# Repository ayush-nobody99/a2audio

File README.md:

# 🎧 a2audio — High-Fidelity Audio DAC/AMP Board

> playback, for the purist.

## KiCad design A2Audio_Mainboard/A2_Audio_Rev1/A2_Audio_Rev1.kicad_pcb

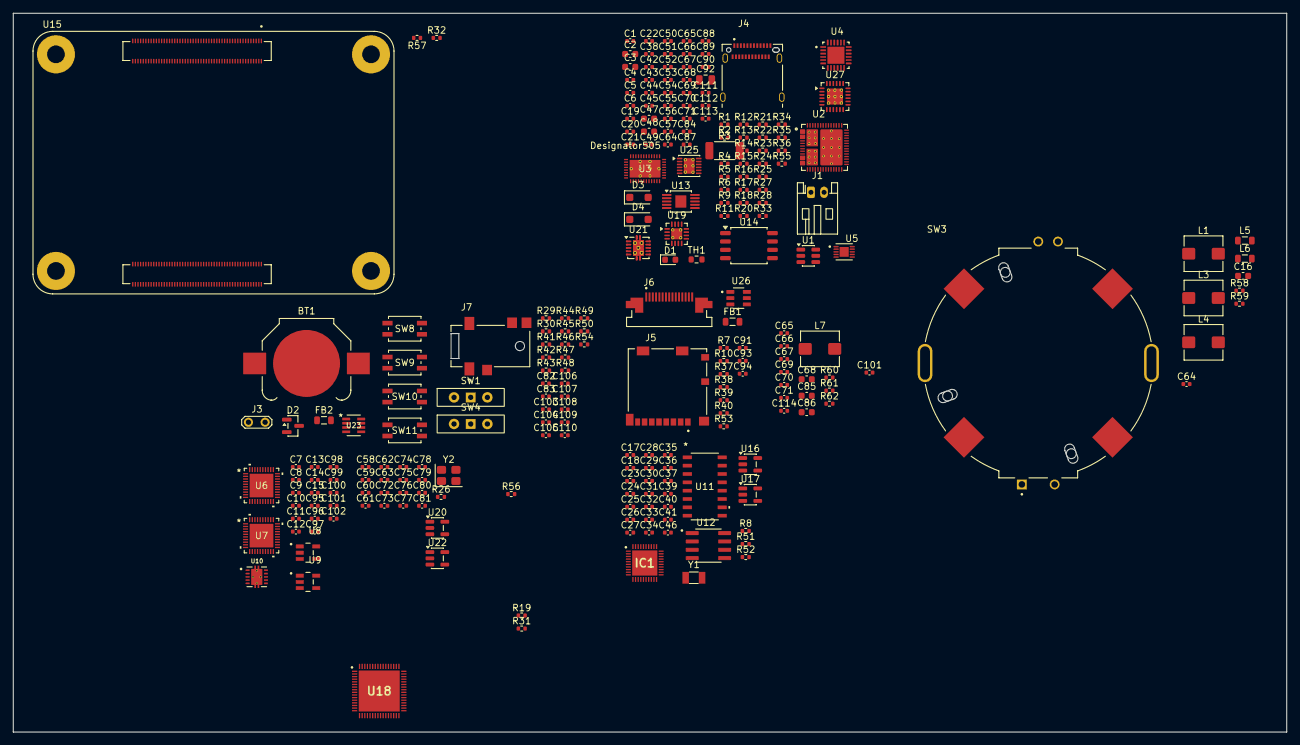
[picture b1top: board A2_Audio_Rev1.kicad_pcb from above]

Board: 4 copper layers, 194.0 x 109.5 mm, 241 parts (0 on the bottom side), 223 nets, no tracks yet.

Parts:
BT1: CR1220; BatteryHolder_Keystone_3000_1x12mm
C1, C7, C8, C9, C39, C40, C41, C46, C71, C96, C97, C99, C100, C103, C113: 1µF; C_0402_1005Metric
C2, C3, C47, C48, C85, C86: 22µF; C_0603_1608Metric
C4, C14, C15, C27, C32, C33, C64, C66#2, C91, C94: 10µF; C_0402_1005Metric
C5, C10, C13, C20, C21, C22, C84, C88, C89, C90, C111: 4.7µF; C_0402_1005Metric
C6: 47nF; C_0402_1005Metric
C11, C12, C24, C25, C34, C35, C36, C37, C53, C95, C98, C101, C102: 2.2µF; C_0402_1005Metric
C16: 10µF; C_0603_1608Metric
C17, C18, C23, C26, C28, C29, C30, C31, C38, C42, C43, C44, C45, C56, C65#2, C67, C83, C87, C112, C114: 0.1µF; C_0402_1005Metric
C19: 0.47µF; C_0402_1005Metric
C49: 3.3nF; C_0402_1005Metric
C50, C51, C52, C64#2, C65, C66, C67#2, C68, C69#2, C70, C71#2, C72, C73, C74, C75, C76, C77, C78, C79, C80, C81, C93, C101#2, C105, C106, C107, C108, C109, C110: 100nF; C_0402_1005Metric
C54: 10nF; C_0402_1005Metric
C55, C57: 22µF; C_0402_1005Metric
C58, C59, C60, C61: 1μF; C_0402_1005Metric
C62, C63: 22pF; C_0402_1005Metric
C68#2: 47nF; C_0603_1608Metric
C69: 4.7nF; C_0402_1005Metric
C70#2: 220pF; C_0402_1005Metric
C82: 0.33µF; C_0402_1005Metric
C92: 22µF; C_0805_2012Metric
C104: 100pF; C_0402_1005Metric
D1: LED; LED_0603_1608Metric
D2: BAT54C; SOT-23
D3, D4: PMEG2020EH; D_SOD-123F
FB1: 600 Ohms @ 100MHz; L_0805_2012Metric
FB2: FerriteBead; L_0805_2012Metric
IC1: ES9822QPRO; QFN40P500X500X80-41N-D
J1: Battery_Connector; JST_PH_S2B-PH-K_1x02_P2.00mm_Horizontal
J3: BOOT_JUMPER; TestPoint_2Pads_Pitch2.54mm_Drill0.8mm
J4: 12401610E4_2A; AMPHENOL_12401610E4_2A
J5: 104031-0811; MOLEX_104031-0811
J6: SFV15R-1STE1HLF; AMPHENOL_SFV15R-1STE1HLF
J7: SJ2-35954B-SMT-TR; CUI_SJ2-35954B-SMT-TR
L1: 1µH; L_Bourns_SRP5030T
L3: 2.2µH; L_Bourns_SRP5030T
L4, L7: 1.0µH; L_Bourns_SRP5030T
L5, L6: 4.7µH; L_0805_2012Metric
R1, R2: 4.7k; R_0402_1005Metric
R3: 10mΩ; R_2010_5025Metric
R4, R5: 45.3kΩ; R_0402_1005Metric
R6, R7, R8, R10, R13, R21, R22, R23, R25, R37, R38, R39, R41, R42, R43, R44, R45, R46, R47, R48, R50, R51, R52, R53, R54, R62: 10kΩ; R_0402_1005Metric
R9: 1kΩ; R_0402_1005Metric
R11: 4.42 kΩ; R_0402_1005Metric
R12: 23.7 kΩ; R_0402_1005Metric
R14, R16, R17, R18, R20, R27, R35, R40, R58, R59: 100kΩ; R_0402_1005Metric
R15: 32.4kΩ; R_0402_1005Metric
R19, R31: 4.7kΩ; R_0402_1005Metric
R24: 180Ω; R_0402_1005Metric
R26: 2kΩ; R_0402_1005Metric
R28: 402kΩ; R_0402_1005Metric
R29: 10k; R_0402_1005Metric
R30: 100k; R_0402_1005Metric
R32, R56, R57: 22Ω; R_0402_1005Metric
R33: 205kΩ; R_0402_1005Metric
R34: 1.0MΩ; R_0402_1005Metric
R36: 124kΩ; R_0402_1005Metric
R49: 2.2kΩ; R_0402_1005Metric
R55: 31.6kΩ; R_0402_1005Metric
R60: 120kΩ; R_0402_1005Metric
R61: 15kΩ; R_0402_1005Metric
SW1, SW4: SW_Wuerth_450301014042; SW_Slide-03_Wuerth-WS-SLTV_10x2.5x6.4_P2.54mm
SW3: RotaryEncoder_Switch; XDCR_RING35-203010-TH
SW8, SW9, SW10, SW11: EVQ-PUJ02K; SW_EVQPUJ_4P7X3P5_PAN
TH1: 10kΩ NTC; R_0603_1608Metric
U1: USBLC6-2SC6; SOT-23-6
U2: TPS65987DDHRSHR; IC_TPS65987DDHRSHR
U3: TUSB546A-DCIRNQR; RNQ0040A
U4: BQ25895RTWR; QFN50P400X400X80-25N
U5: MAX17055ETB_T; SON40P200X250X80-11N
U6: U_DAC_L; QFN_CS43198_CIR
U7: U_DAC_R; QFN_CS43198_CIR
U8: TPS7A2018PDBVR; SOT95P280X145-5N
U9: TPS7A2033PDBVR; SOT95P280X145-5N
U10: OPA1622IDRCR; IC_OPA1622IDRCR
U11: SI4732-A10-GS; SOIC_A10-GS_SIL
U12: OPA1612AIDR; SOIC127P599X175-8N
U13: LT3042xMSE; MSOP-10-1EP_3x3mm_P0.5mm_EP1.68x1.88mm
U14: W25Q16JVSS; SOIC-8_5.3x5.3mm_P1.27mm
U15: CM5108000; MODULE_CM5108000
U16: AP2112K-3.3; SOT-23-5
U17, U20: AP2112K-1.8; SOT-23-5
U18: LT6711A; QFN40P750X750X80-65N-D
U19: TPS62130; VQFN-16-1EP_3x3mm_P0.5mm_EP1.68x1.68mm_ThermalVias
U21: TPS61230DRC; Texas_S-PVSON-N10_ThermalVias
U22: AP2112K-1.2; SOT-23-5
U23: LTC2954ITS8-1_TRPBF; TSOT-23_TS8
U25: LT3094xDD; DFN-12-1EP_3x3mm_P0.45mm_EP1.65x2.38mm_ThermalVias
U26: TS5A3159DBVR; SOT95P280X145-6N
U27: TPS65131RGE; VQFN-24-1EP_4x4mm_P0.5mm_EP2.45x2.45mm_ThermalVias
Y1: Crystal; Crystal_SMD_3215-2Pin_3.2x1.5mm
Y2: 27MHz; Crystal_SMD_3225-4Pin_3.2x2.5mm

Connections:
+5V(INPUT): C55.1, C56.1, C57.1, C85.1, C86.1, C114.1, R28.1, U15.77 (+5V(INPUT)), U15.79 (+5V(INPUT)), U15.81 (+5V(INPUT)), U15.83 (+5V(INPUT)), U15.85 (+5V(INPUT)), U15.87 (+5V(INPUT)), U21.3 (VOUT), U21.4 (VOUT)
/+3V3_SYS: C48.1, C51.1, C58.1, C59.2, C91.1, C93.1, C101#2.1, J5.4 (VDD), J6.14, J6.15, L3.2, R14.2, R16.1, R58.2, U2.5 (VIN_3V3), U3.1 (VCC), U3.6 (VCC), U3.20 (VCC), U3.28 (VCC), U18.8 (VCC33R), U18.20 (VCC33IO), U18.21 (VDD), U18.30 (VCC33STBY), U18.55 (VDD), U18.57 (VCC33IO), U19.14 (VOS), U20.1 (VIN), U20.3 (EN), U22.1 (VIN), U22.3 (EN), U26.3 (NC), U26.5 (V+)
/Audio_Engine/1V8_DIG: C8.1, U6.4 (VD), U6.7 (VA), U6.25 (VCP), U6.28 (*RESET), U6.31 (VL), U7.4 (VD), U7.7 (VA), U7.25 (VCP), U7.28 (*RESET), U7.30 (ADR), U7.31 (VL), U8.5 (OUT)
/Audio_Engine/3V3_ANA: C9.1, R19.2, R31.2, U6.26 (VP), U7.26 (VP), U9.5 (OUT), U10.8 (EN)
/Audio_Engine/AUDIO_OUT_L: U6.14 (HPOUTA), U10.1 (+INA)
/Audio_Engine/AUDIO_OUT_R: U7.14 (HPOUTA), U10.5 (+INB)
/Audio_Engine/HP_OUT_L: J7.2, U10.9 (OUTA), U10.10 (-INA)
/Audio_Engine/HP_OUT_R: J7.3, U10.6 (-INB), U10.7 (OUTB)
/BAT_ALRT: R21.1, U5.8 (ALRT), U15.30 (GPIO6)
/BT: R43.1, SW1.1 (B), U15.91 (BT_~DISABLE)
/BTN_INT: R29.2, U15.29 (GPIO16), U23.5 (*INT)
/BTN_KILL: R30.2, U15.24 (GPIO26), U23.8 (*KILL)
/CARD_DETECT: J5.10 (SW-2), R53.1, U15.37 (GPIO7)
/CHG_INT: R22.1, U4.7 (INT), U15.34 (GPIO5)
/ENC_1: C105.1, R42.2, SW3.A, U15.38 (GPIO11)
/ENC_2: C106.1, R44.2, SW3.B, U15.39 (GPIO8)
/ENC_SW: C107.1, R45.2, U15.40 (GPIO9)
/FM_ANT: C104.2, U11.6 (FMI)
/HP_DETECT: J7.10, R54.1, U15.55 (GPIO14)
/HP_GOOD_OUT: R6.1, U13.4 (PG), U15.47 (GPIO23), U25.4 (PG)
/I2C_SCL: R2.2, U2.27 (I2C1_SCL), U4.5 (SCL), U5.3 (SCL), U11.11 (SCLK), U15.56 (GPIO3), U18.17 (CSCL)
/I2C_SCL_AUDIO: IC1.26 (SCLK/SCL), R19.1, U6.1 (SCL), U7.1 (SCL), U15.28 (GPIO13)
/I2C_SDA: R1.2, U2.28 (I2C1_SDA), U4.6 (SDA), U5.4 (SDA), U11.12 (SDIO), U15.58 (GPIO2), U18.16 (CSDA)
/I2C_SDA_AUDIO: IC1.25 (MOSI/SDA), R31.1, U6.39 (SDA), U7.39 (SDA), U15.31 (GPIO12)
/I2S_BCLK: IC1.38 (GPIO2), U6.34 (SCLK1), U7.34 (SCLK1), U15.49 (GPIO18)
/I2S_DATA_IN: U6.2 (SDIN1), U7.2 (SDIN1), U15.25 (GPIO21)
/I2S_DATA_OUT: IC1.39 (GPIO1), U15.27 (GPIO20)
/I2S_LRCLK: IC1.37 (GPIO3), U6.38 (LRCK1), U7.38 (LRCK1), U15.26 (GPIO19)
/I2S_MCLK: R32.2, R56.1, R57.2, U15.54 (GPIO4)
/MIC_IN: R50.2, R51.2, U12.3 (+IN_A)
/MIPI1_C_N: J6.5, U15.187 (MIPI1_C_N)
/MIPI1_C_P: J6.6, U15.189 (MIPI1_C_P)
/MIPI1_D0_N: J6.8, U15.175 (MIPI1_D0_N)
/MIPI1_D0_P: J6.9, U15.177 (MIPI1_D0_P)
/MIPI1_D1_N: J6.2, U15.181 (MIPI1_D1_N)
/MIPI1_D1_P: J6.3, U15.183 (MIPI1_D1_P)
/NEXT: C109.1, R47.2, SW10.1, U15.45 (GPIO24)
/PD_IRQ: R25.1, U2.29 (~I2C1_IRQ), U15.46 (GPIO22)
/PLAY: C110.1, R48.2, SW11.1, U15.44 (GPIO10)
/PMIC_EN: U15.99 (PMIC_ENABLE), U23.6 (EN/*EN)
/PREV: C108.1, R46.2, SW9.1, U15.41 (GPIO25)
/PWR_BUTTON: D2.1, U4.12 (~QON)
/Power&Battery/+6V_DIRTY: C20.2, C84.1, C87.1, D3.1 (K), R36.2, U13.1 (IN), U13.2 (IN), U13.3 (EN/UV), U13.6 (PGFB), U27.23 (VPOS)
/Power&Battery/-6V_DIRTY: C90.2, C111.1, C112.1, D4.2 (A), R34.2, U25.1 (IN), U25.2 (IN), U25.3 (EN/UV), U25.5 (PGFB), U25.7 (VIOC), U25.13 (IN), U27.15 (VNEG)
/Power&Battery/BATTERY_NEG: J1.2, R3.1, U5.5 (CSN)
/Power&Battery/BTST_CAP: C6.1, U4.21 (BTST)
/Power&Battery/CABLE_FLIP: U2.16 (GPIO0), U3.21 (FLIP_SCL)
/Power&Battery/CC11: J4.A5 (CC1), U2.24 (C_CC1)
/Power&Battery/CC21: J4.B5 (CC2), U2.26 (C_CC2)
/Power&Battery/D+1: J4.A6 (D1+), J4.B6 (D2+), U1.3 (I/O2)
/Power&Battery/D-1: J4.A7 (D1-), J4.B7 (D2-), U1.1 (I/O1)
/Power&Battery/DP_AUX_N: C80.1, R58.1, U3.25 (AUXN)
/Power&Battery/DP_AUX_P: C81.1, R59.1, U3.24 (AUXP)
/Power&Battery/DP_HPD: U2.30 (GPIO3(HPD)), U3.32 (HPDIN_DCI_CLK2), U18.26 (DTXHPD_DVDET_G10)
/Power&Battery/DP_LANE0_N: C73.2, U3.10 (DP0N)
/Power&Battery/DP_LANE0_P: C72.2, U3.9 (DP0P)
/Power&Battery/DP_LANE1_N: C75.2, U3.13 (DP1N)
/Power&Battery/DP_LANE1_P: C74.2, U3.12 (DP1P)
/Power&Battery/DP_LANE2_N: C77.2, U3.16 (DP2N)
/Power&Battery/DP_LANE2_P: C76.2, U3.15 (DP2P)
/Power&Battery/DP_LANE3_N: C79.2, U3.19 (DP3N)
/Power&Battery/DP_LANE3_P: C78.2, U3.18 (DP3P)
/Power&Battery/REGN: C5.1, R11.1, U4.22 (REGN)
/Power&Battery/RX1+1: J4.B11 (RX1+), U3.30 (RX1P)
/Power&Battery/RX1-1: J4.B10 (RX1-), U3.31 (RX1N)
/Power&Battery/RX2+1: J4.A11 (RX2+), U3.40 (RX2P)
/Power&Battery/RX2-1: J4.A10 (RX2-), U3.39 (RX2N)
/Power&Battery/SBU1: J4.A8 (SBU1), U3.27 (SBU1)
/Power&Battery/SBU2: J4.B8 (SBU2), U3.26 (SBU2)
/Power&Battery/TX1+1: C43.1, J4.A2 (TX1+)
/Power&Battery/TX1-1: C42.1, J4.A3 (TX1-)
/Power&Battery/TX2+1: C45.1, J4.B2 (TX2+)
/Power&Battery/TX2-1: C44.1, J4.B3 (TX2-)
/Power&Battery/TYPEC_TX1_N: C42.2, U3.34 (TX1N)
/Power&Battery/TYPEC_TX1_P: C43.2, U3.33 (TX1P)
/Power&Battery/TYPEC_TX2_N: C44.2, U3.36 (TX2N)
/Power&Battery/TYPEC_TX2_P: C45.2, U3.37 (TX2P)
/Power&Battery/USB2_D_N: U1.6 (I/O1), U2.53 (C_USB_N(GPIO19)), U15.103 (USB_N)
/Power&Battery/USB2_D_P: U1.4 (I/O2), U2.50 (C_USB_P(GPIO18)), U15.105 (USB_P)
/Power&Battery/VBUS_PD: C1.2, U2.1 (PP_HV2), U2.7 (DRAIN2), U2.8 (DRAIN1), U2.11 (PP_HV1), U2.15 (DRAIN1), U2.19 (DRAIN1), U2.52 (DRAIN2), U2.56 (DRAIN2), U2.57 (DRAIN2), U2.57_1 (DRAIN2), U2.57_2 (DRAIN2), U2.57_3 (DRAIN2), U2.57_4 (DRAIN2), U2.57_5 (DRAIN2), U2.57_6 (DRAIN2), U2.58 (DRAIN1), U2.58_1 (DRAIN1), U2.58_2 (DRAIN1), U2.58_3 (DRAIN1), U2.58_4 (DRAIN1), U2.58_5 (DRAIN1), U2.58_6 (DRAIN1), U4.1 (VBUS)
/RPI_BOOT: J3.1, U15.93 (~RPIBOOT)
/Recording&Radio_Engine/3v: C23.1, C26.1, C27.2, C30.2, C41.1, IC1.23 (CHIP_EN), IC1.30 (AVDD), R8.2, U11.14 (VDD), U16.5 (VOUT)
/Recording&Radio_Engine/+5V_AMP: C18.2, C21.2, C28.2, C29.2, C31.2, C39.1, C40.1, IC1.5 (AVCC), IC1.10 (AVCC_L), IC1.21 (AVCC_R), U10.2 (V+), U12.8 (V+), U13.9 (OUTS), U13.10 (OUT), U16.1 (VIN), U16.3 (EN), U17.1 (VIN), U17.3 (EN)
/SCL: J6.11, U15.80 (SCL0)
/SDA: J6.12, U15.82 (SDA0)
/SD_CLK: J5.5 (CLK), U15.57 (SD_CLK)
/SD_CMD: J5.3 (CMD), R7.1, U15.62 (SD_CMD)
/SD_DAT0: J5.7 (DAT0), R37.1, U15.63 (SD_DAT0)
/SD_DAT1: J5.8 (DAT1), R10.1, U15.67 (SD_DAT1)
/SD_DAT2: J5.1 (DAT2), R38.1, U15.69 (SD_DAT2)
/SD_DAT3: J5.2 (CD/DAT3), R39.1, U15.61 (SD_DAT3)
/USB3_RX_N: U3.4 (SSRXN), U15.128 (USB3-0-RX_N)
/USB3_RX_P: U3.5 (SSRXP), U15.130 (USB3-0-RX_P)
/USB3_TX_N: U3.7 (SSTXN), U15.140 (USB3-0-TX_N)
/USB3_TX_P: U3.8 (SSTXP), U15.142 (USB3-0-TX_P)
/USB_OTG_ID: U2.17 (GPIO1), U15.101 (USB_OTG_ID)
/VBUS_EN: U4.8 (OTG), U15.111 (VBUS_EN)
/VDD_OVERRIDE: R40.1, U15.73 (SD_VDD_OVERRIDE), U15.75 (SD_PWR_ON), U26.6 (IN)
/VID_IRQ: U15.48 (GPIO27), U18.29 (IRQ0_G11)
/VID_RST: U15.50 (GPIO17), U18.56 (RST_N)
/Video_Engine/+1V2_VID: C60.2, U18.2 (VCC12R), U18.5 (VCC12R), U18.11 (VCC12R), U18.14 (VCC12_RXPLL), U18.15 (VCC12R), U18.32 (VCC12A), U18.35 (VCC12T), U18.46 (VCC12T), U22.5 (VOUT)
/Video_Engine/+1V8_VID: C61.2, FB1.2, U18.38 (VCC18T), U18.43 (VCC18T), U20.5 (VOUT)
/Video_Engine/HDMI_CEC: U15.151 (HDMI0_CEC), U18.1 (CEC_G5)
/Video_Engine/HDMI_CLK_N: U15.190 (HDMI0_CLK_N), U18.3 (HCN)
/Video_Engine/HDMI_CLK_P: U15.188 (HDMI0_CLK_P), U18.4 (HCP)
/Video_Engine/HDMI_HPD: U15.153 (HDMI0_HOTPLUG), U18.58 (HRXHPD_G0)
/Video_Engine/HDMI_SCL: U15.200 (HDMI0_SCL), U18.59 (DSCL_G1)
/Video_Engine/HDMI_SDA: U15.199 (HDMI0_SDA), U18.60 (DSDA_G2)
/Video_Engine/HDMI_TX0_N: U15.184 (HDMI0_TX0_N), U18.6 (H0N)
/Video_Engine/HDMI_TX0_P: U15.182 (HDMI0_TX0_P), U18.7 (H0P)
/Video_Engine/HDMI_TX1_N: U15.178 (HDMI0_TX1_N), U18.9 (H1N)
/Video_Engine/HDMI_TX1_P: U15.176 (HDMI0_TX1_P), U18.10 (H1P)
/Video_Engine/HDMI_TX2_N: U15.172 (HDMI0_TX2_N), U18.12 (H2N)
/Video_Engine/HDMI_TX2_P: U15.170 (HDMI0_TX2_P), U18.13 (H2P)
/Vital_Engine/+V_SD_IO: R7.2, R10.2, R37.2, R38.2, R39.2, U26.4 (COM)
/WIFI: R41.1, SW4.1 (B), U15.89 (WL_~DISABLE)
BAT: C4.2, J1.1, U4.13 (BAT), U4.14 (BAT), U5.10 (BATT)
CM5_1.8V(OUTPUT): U15.88 (CM5_1.8V(OUTPUT)), U15.90 (CM5_1.8V(OUTPUT))
CM5_3.3V(OUTPUT): R6.2, R21.2, R22.2, R25.2, R29.1, R30.1, R41.2, R42.1, R43.2, R44.1, R45.1, R46.1, R47.1, R48.1, R49.1, R53.2, R54.2, U15.78 (GPIO_VREF), U15.84 (CM5_3.3V(OUTPUT)), U15.86 (CM5_3.3V(OUTPUT))
EXP: C17.1, C92.2, U10.4 (V-), U10.11 (EXP), U10.12 (EXP), U10.13 (EXP), U10.14 (EXP), U10.15 (EXP), U12.4 (V-), U25.10 (OUTS), U25.11 (OUT), U25.12 (OUT)
GND: BT1.2 (-), C1.1, C2.2, C3.2, C4.1, C5.2, C7.2, C8.2, C9.2, C11.2, C12.2, C14.2, C15.2, C16.2, C17.2, C18.1, C19.2, C20.1, C21.1, C22.2, C23.2, C26.2, C27.1, C28.1, C29.1, C30.1, C31.1, C32.1, C33.1, C35.1, C37.1, C38.1, C39.2, C40.2, C41.2, C46.2, C47.2, C48.2, C49.2, C50.2, C51.2, C52.1, C53.2, C54.1, C55.2, C56.2, C57.2, C58.2, C59.1, C60.1, C61.1, C62.2, C63.2, C64.1, C65#2.2, C66#2.2, C68#2.2, C69.2, C70#2.1, C71.1, C71.2, C82.2, C83.2, C84.2, C85.2, C86.2, C87.2, C89.2, C90.1, C91.2, C92.1, C93.2, C94.2, C101#2.2, C105.2, C106.2, C107.2, C108.2, C109.2, C110.2, C111.2, C112.2, C113.2, C114.2, FB2.2, IC1.3 (MODE), IC1.6 (AGND), IC1.11 (AGND_L), IC1.20 (AGND_R), IC1.27 (SS/ADDR1), IC1.28 (MISO/ADDR2), IC1.31 (DGND_1), IC1.40 (DGND_2), IC1.41 (DGND_3), J3.2, J4.A1 (GND_A), J4.A12 (GND_A), J4.B1 (GND_B), J4.B12 (GND_B), J4.SH1 (SHIELD), J4.SH2 (SHIELD), J4.SH3 (SHIELD), J4.SH4 (SHIELD), J5.6 (VSS), J5.9 (SW-1), J5.G1 (GND), J5.G2 (GND), J5.G3 (GND), J5.G4 (GND), J6.1, J6.4, J6.7, J6.10, J6.13, L6.2, R3.2, R4.2, R5.2, R12.2, R13.2, R15.2, R17.2, R20.2, R23.2, R24.1, R26.1, R27.2, R35.1, R40.2, R55.1, R59.2, R60.1, R61.2, SW1.2 (C), SW3.C, SW4.2 (C), SW8.2, SW9.2, SW10.2, SW11.2, TH1.2, U1.2 (GND), U2.20 (GND), U2.45 (GND), U2.46 (GND), U2.47 (GND), U2.51 (GND), U2.59 (GND), U2.59_1 (GND), U2.59_2 (GND), U2.59_3 (GND), U2.59_4 (GND), U2.59_5 (GND), U2.59_6 (GND), U2.59_7 (GND), U2.59_8 (GND), U2.59_9 (GND), U2.59_10 (GND), U2.59_11 (GND), U3.17 (I2C_EN), U3.41 (PAD), U4.9 (~CE), U4.17 (PGND), U4.18 (PGND), U4.25 (POWERPAD), U5.1 (GND), U5.2 (AIN), U5.6 (CSP), U5.11 (EP), U6.8 (GNDA), U6.19 (GNDCP), U6.30 (ADR), U6.35 (GNDD), U6.41 (EPAD), U7.8 (GNDA), U7.19 (GNDCP), U7.35 (GNDD), U7.41 (EPAD), U8.2 (GND), U9.2 (GND), U10.3 (GND), U11.7 (RFGND), U11.8 (AMI), U11.10 (SENB), U11.15 (GND), U13.8 (GND), U13.11 (GND), U14.4 (GND), U15.1 (GND), U15.2 (GND), U15.7 (GND), U15.8 (GND), U15.13 (GND), U15.14 (GND), U15.22 (GND), U15.23 (GND), U15.32 (GND), U15.33 (GND), U15.42 (GND), U15.43 (GND), U15.52 (GND), U15.53 (GND), U15.59 (GND), U15.60 (GND), U15.65 (GND), U15.66 (GND), U15.71 (GND), U15.74 (GND), U15.98 (GND), U15.107 (GND), U15.108 (GND), U15.113 (GND), U15.114 (GND), U15.119 (GND), U15.120 (GND), U15.125 (GND), U15.126 (GND), U15.131 (GND), U15.132 (GND), U15.137 (GND), U15.138 (GND), U15.144 (GND), U15.150 (GND), U15.155 (GND), U15.156 (GND), U15.161 (GND), U15.162 (GND), U15.167 (GND), U15.168 (GND), U15.173 (GND), U15.174 (GND), U15.179 (GND), U15.180 (GND), U15.185 (GND), U15.186 (GND), U15.191 (GND), U15.192 (GND), U15.197 (GND), U15.198 (GND), U15.SH1 (MOUNTING_PADS), U15.SH2 (MOUNTING_PADS), U15.SH3 (MOUNTING_PADS), U15.SH4 (MOUNTING_PADS), U16.2 (GND), U17.2 (GND), U18.65 (EP), U19.6 (GND), U19.7 (FSW), U19.8 (DEF), U19.15 (GND), U19.16 (GND), U19.17 (GND), U20.2 (GND), U21.11 (GND), U22.2 (GND), U23.4 (GND), U25.9 (GND), U26.2 (GND), U27.2 (PGND), U27.3 (PGND), U27.19 (AGND), U27.25 (EP), Y1.2, Y2.2 (G), Y2.4 (G)
unnamed: BT1.1 (+), U15.76 (VBAT)
unnamed: C24.1, R51.1
unnamed: C25.2, R52.1
unnamed: C69.1, R62.2
unnamed: C103.1, J7.1, R49.2
unnamed: C103.2, R50.1
unnamed: C104.1, FB2.1, J7.4
unnamed: D1.2 (A), R9.1
unnamed: D1.1 (K), U4.4 (STAT)
unnamed: D2.3, SW8.1
unnamed: D3.2 (A), L5.2, U27.7 (BSW)
unnamed: D4.1 (K), L6.1, U27.13 (OUTN), U27.14 (OUTN)
unnamed: C64.2, IC1.29 (DVDD)
unnamed: C35.2, IC1.13 (IN_M1)
unnamed: C37.2, IC1.18 (IN_M2)
unnamed: C34.2, IC1.12 (IN_P1)
unnamed: C36.2, IC1.19 (IN_P2)
unnamed: C32.2, IC1.9 (VREF_L)
unnamed: C33.2, IC1.22 (VREF_R)
unnamed: IC1.8 (XIN), R56.2
unnamed: L3.1, U19.1 (SW), U19.2 (SW), U19.3 (SW)
unnamed: L4.1, U21.1 (SW), U21.2 (SW)
unnamed: R17.1, R18.2, U2.6 (ADCIN1)
unnamed: R20.1, R35.2, U2.10 (ADCIN2)
unnamed: U2.54 (GPIO20), U3.22 (CTL0_SDA)
unnamed: U2.55 (GPIO21), U3.23 (CTL1_HPDIN)
unnamed: C52.2, R16.2, U2.44 (HRESET)
unnamed: C53.1, U2.35 (LDO_1V8)
unnamed: C2.1, U2.25 (PP_CABLE), U4.23 (PMID)
unnamed: R13.1, U3.29 (CAD_SNK_DCI_DAT)
unnamed: R24.2, U4.10 (ILIM)
unnamed: R11.2, R12.1, TH1.1, U4.11 (TS)
unnamed: C19.1, U5.7 (REG)
unnamed: R23.1, U5.9 (THRM)
unnamed: C11.1, C101.1, U6.9 (-VA)
unnamed: C14.1, U6.5 (FILT+)
unnamed: C101.2, U6.6 (FILT-)
unnamed: C100.2, U6.23 (FLYC_VCP)
unnamed: C10.1, U6.11 (FLYN_VA)
unnamed: C99.2, U6.20 (FLYN_VCP)
unnamed: C10.2, U6.10 (FLYP_VA)
unnamed: C99.1, C100.1, U6.24 (FLYP_VCP)
unnamed: C98.1, U6.21 (VCP_FILT+)
unnamed: C98.2, U6.18 (VCP_FILT-)
unnamed: R57.1, U6.37 (XTI/MCLK)
unnamed: C12.1, C102.1, U7.9 (-VA)
unnamed: C15.1, U7.5 (FILT+)
unnamed: C102.2, U7.6 (FILT-)
unnamed: C97.2, U7.23 (FLYC_VCP)
unnamed: C13.1, U7.11 (FLYN_VA)
unnamed: C96.2, U7.20 (FLYN_VCP)
unnamed: C13.2, U7.10 (FLYP_VA)
unnamed: C96.1, C97.1, U7.24 (FLYP_VCP)
unnamed: C95.1, U7.21 (VCP_FILT+)
unnamed: C95.2, U7.18 (VCP_FILT-)
unnamed: R32.1, U7.37 (XTI/MCLK)
unnamed: R8.1, U11.9 (*RST)
unnamed: C24.2, U11.1 (LOUT/DFS)
unnamed: U11.13 (RCLK), Y1.1
unnamed: C25.1, U11.16 (ROUT/DOUT)
unnamed: R52.2, U12.5 (+IN_B)
unnamed: C34.1, U12.1 (OUT_A), U12.2 (-IN_A)
unnamed: C36.1, U12.6 (-IN_B), U12.7 (OUT_B)
unnamed: C22.1, R4.1, U13.7 (SET)
unnamed: U2.38 (SPI_CLK), U14.6 (CLK)
unnamed: U2.37 (SPI_MOSI), U14.5 (DI/IO_{0})
unnamed: U2.36 (SPI_MISO), U14.2 (DO/IO_{1})
unnamed: C16.1, C38.2, R1.1, R2.1, R18.1, U2.9 (LDO_3V3), U14.3 (~WP/IO_{2}), U14.7 (~HOLD/~RESET/IO_{3}), U14.8 (VCC)
unnamed: U2.39 (~SPI_SS), U14.1 (~CS)
unnamed: C70#2.2, R62.1
unnamed: C67.2, L7.1
unnamed: C46.1, U17.5 (VOUT)
unnamed: C80.2, U18.23 (AUXN)
unnamed: C81.2, U18.24 (AUXP)
unnamed: C73.1, U18.47 (D0N/B10_RX1N)
unnamed: C72.1, U18.48 (D0P/B11_RX1P)
unnamed: C75.1, U18.41 (D1N/A10_RX2N)
unnamed: C74.1, U18.42 (D1P/A11_RX2P)
unnamed: C77.1, U18.39 (D2N/A2_TX1P)
unnamed: C76.1, U18.40 (D2P/A3_TX1N)
unnamed: C79.1, U18.33 (D3N/B2_TX2P)
unnamed: C78.1, U18.34 (D3P/B3_TX2N)
unnamed: R26.2, U18.31 (REXT)
unnamed: C62.1, U18.19 (XTALI), Y2.1
unnamed: C63.1, U18.18 (XTALO), Y2.3
unnamed: R14.1, R15.1, U19.5 (FB)
unnamed: C49.1, U19.9 (SS/TR)
unnamed: R27.1, R28.2, U21.7 (FB)
unnamed: C54.2, U21.6 (SS)
unnamed: D2.2, U23.2 (*PB)
unnamed: C83.1, U23.3 (ONT)
unnamed: C82.1, U23.7 (PDT)
unnamed: C89.1, R5.1, U25.8 (SET)
unnamed: C94.1, FB1.1, U26.1 (NO)
unnamed: C88.1, U27.18 (CN)
unnamed: C88.2, U27.21 (CP)
unnamed: R33.2, R34.1, U27.16 (FBN)
unnamed: R36.1, R55.2, U27.22 (FBP)
unnamed: C113.1, R33.1, U27.17 (VREF)
SW: C6.2, L1.1, U4.19 (SW), U4.20 (SW)
SYS: C3.1, C7.1, C47.1, C50.1, C65#2.1, C66#2.1, L1.2, L4.2, L5.1, L7.2, R9.2, U4.15 (SYS), U4.16 (SYS), U8.1 (IN), U8.3 (EN), U9.1 (IN), U9.3 (EN), U19.10 (VIN), U19.11 (VIN), U19.12 (VIN), U19.13 (EN), U21.9 (EN), U21.10 (VIN), U23.1 (VIN), U27.1 (INP), U27.4 (VIN), U27.5 (INN), U27.6 (INN), U27.8 (ENP), U27.9 (PSP), U27.10 (ENN), U27.11 (PSN), U27.24 (INP)
VBUS_A: J4.A4 (VBUS_A), J4.A9 (VBUS_A), J4.B4 (VBUS_B), J4.B9 (VBUS_B), U1.5 (VBUS), U2.3 (VBUS2), U2.13 (VBUS1)

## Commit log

2026-05-18 INITIAL A2AUDIO UPLOAD
2026-05-20 Added the new kicad footprints for each schematic, that didn't have one previously (most of them).
2026-05-20 Cleanup of directories and addition of README file.
2026-05-20 More directory refinement.
2026-05-23 Added footprints and a few more parts.
2026-05-23 More Refinement
2026-05-24 Refining of logic and adding battery connector
2026-05-24 Fixing ERC errors
2026-05-26 Added fixes for ERC errors
2026-05-26 Added ERC error corrections
2026-05-27 Fixed repo cloning
2026-05-28 Fixed even more schematic errors
2026-06-02 Final touches in schematic
2026-06-13 Fixed SD Card logic and power error
